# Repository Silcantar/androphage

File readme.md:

# Androphage

There have been keyboards that are portable and there have been keyboards that
have integrated pointing devices, but to date there haven't been any keyboards
that combine both features. With this new design I intend to change that.

I'm reaching the end of the design phase on my new keyboard, Androphage. It's a
folding unibody split keyboard with 44 keys and a finger trackball in the
center. When the keyboard is closed, all the more delicate components ---
switches, keycaps, screen --- are protected inside the rugged SLS nylon case.
Additionally the trackball is secured in-place by the folding base of the
keyboard.

## Highlights:

- Unibody with fixed 15° split angle\* and 10° tent angle.

- 44 keys: 3x5, plus 4 thumb keys, row 5\*\* middle and ring finger keys, and
  key that can either be a very tucked thumb key or a row 5 index finger key.

- Rugged SLS nylon case.

- NRF52850 microcontroller and ZMK firmware for Bluetooth, dongle, or wired
  connectivity.

- Dual-sensor 34mm trackball is capable of 3-axis control, i.e. twist-to-scroll
  à la Kensington SlimBlade.

- Nice!View or similar screen for layer, pairing, and charging status.

- Low power consumption microcontroller and trackball sensors (PMW3610) paired
  with a 300 mAh LiPo battery for days or weeks of battery life.

- USB-C charging and connectivity.

- Designed for Chicago Steno or KLP Lamé keycaps but can potentially be adapted
  for other low-to-mid-profile keycaps.

- The custom hinges are SLM stainless steel for maximum durability.

- There is space inside the base for storing the charging cable.

- Unfolded dimensions: 290 x 135 x 62 mm

- Folded dimensions: 148 x 135 x 45 mm

\* Measured between the centerline of the keyboard and the axis of the index
finger key column.

\*\* That is, two rows below the home row, equivalent to the modifier row on an
ANSI/ISO keyboard.

## Additional Renders

## Open Source

This project is licensed under the CERN Open Hardware License, Strongly
Reciprocal 2.0.

---

> *Well, I saw the thing comin' out of the sky*
>
> *It had a-one long horn and one big eye*
>
> *I commenced to shakin' and I said, "Ooh-eee!*
>
> *It looks like a purple people eater to me!"*
>
> &mdash;Sheb Wooley

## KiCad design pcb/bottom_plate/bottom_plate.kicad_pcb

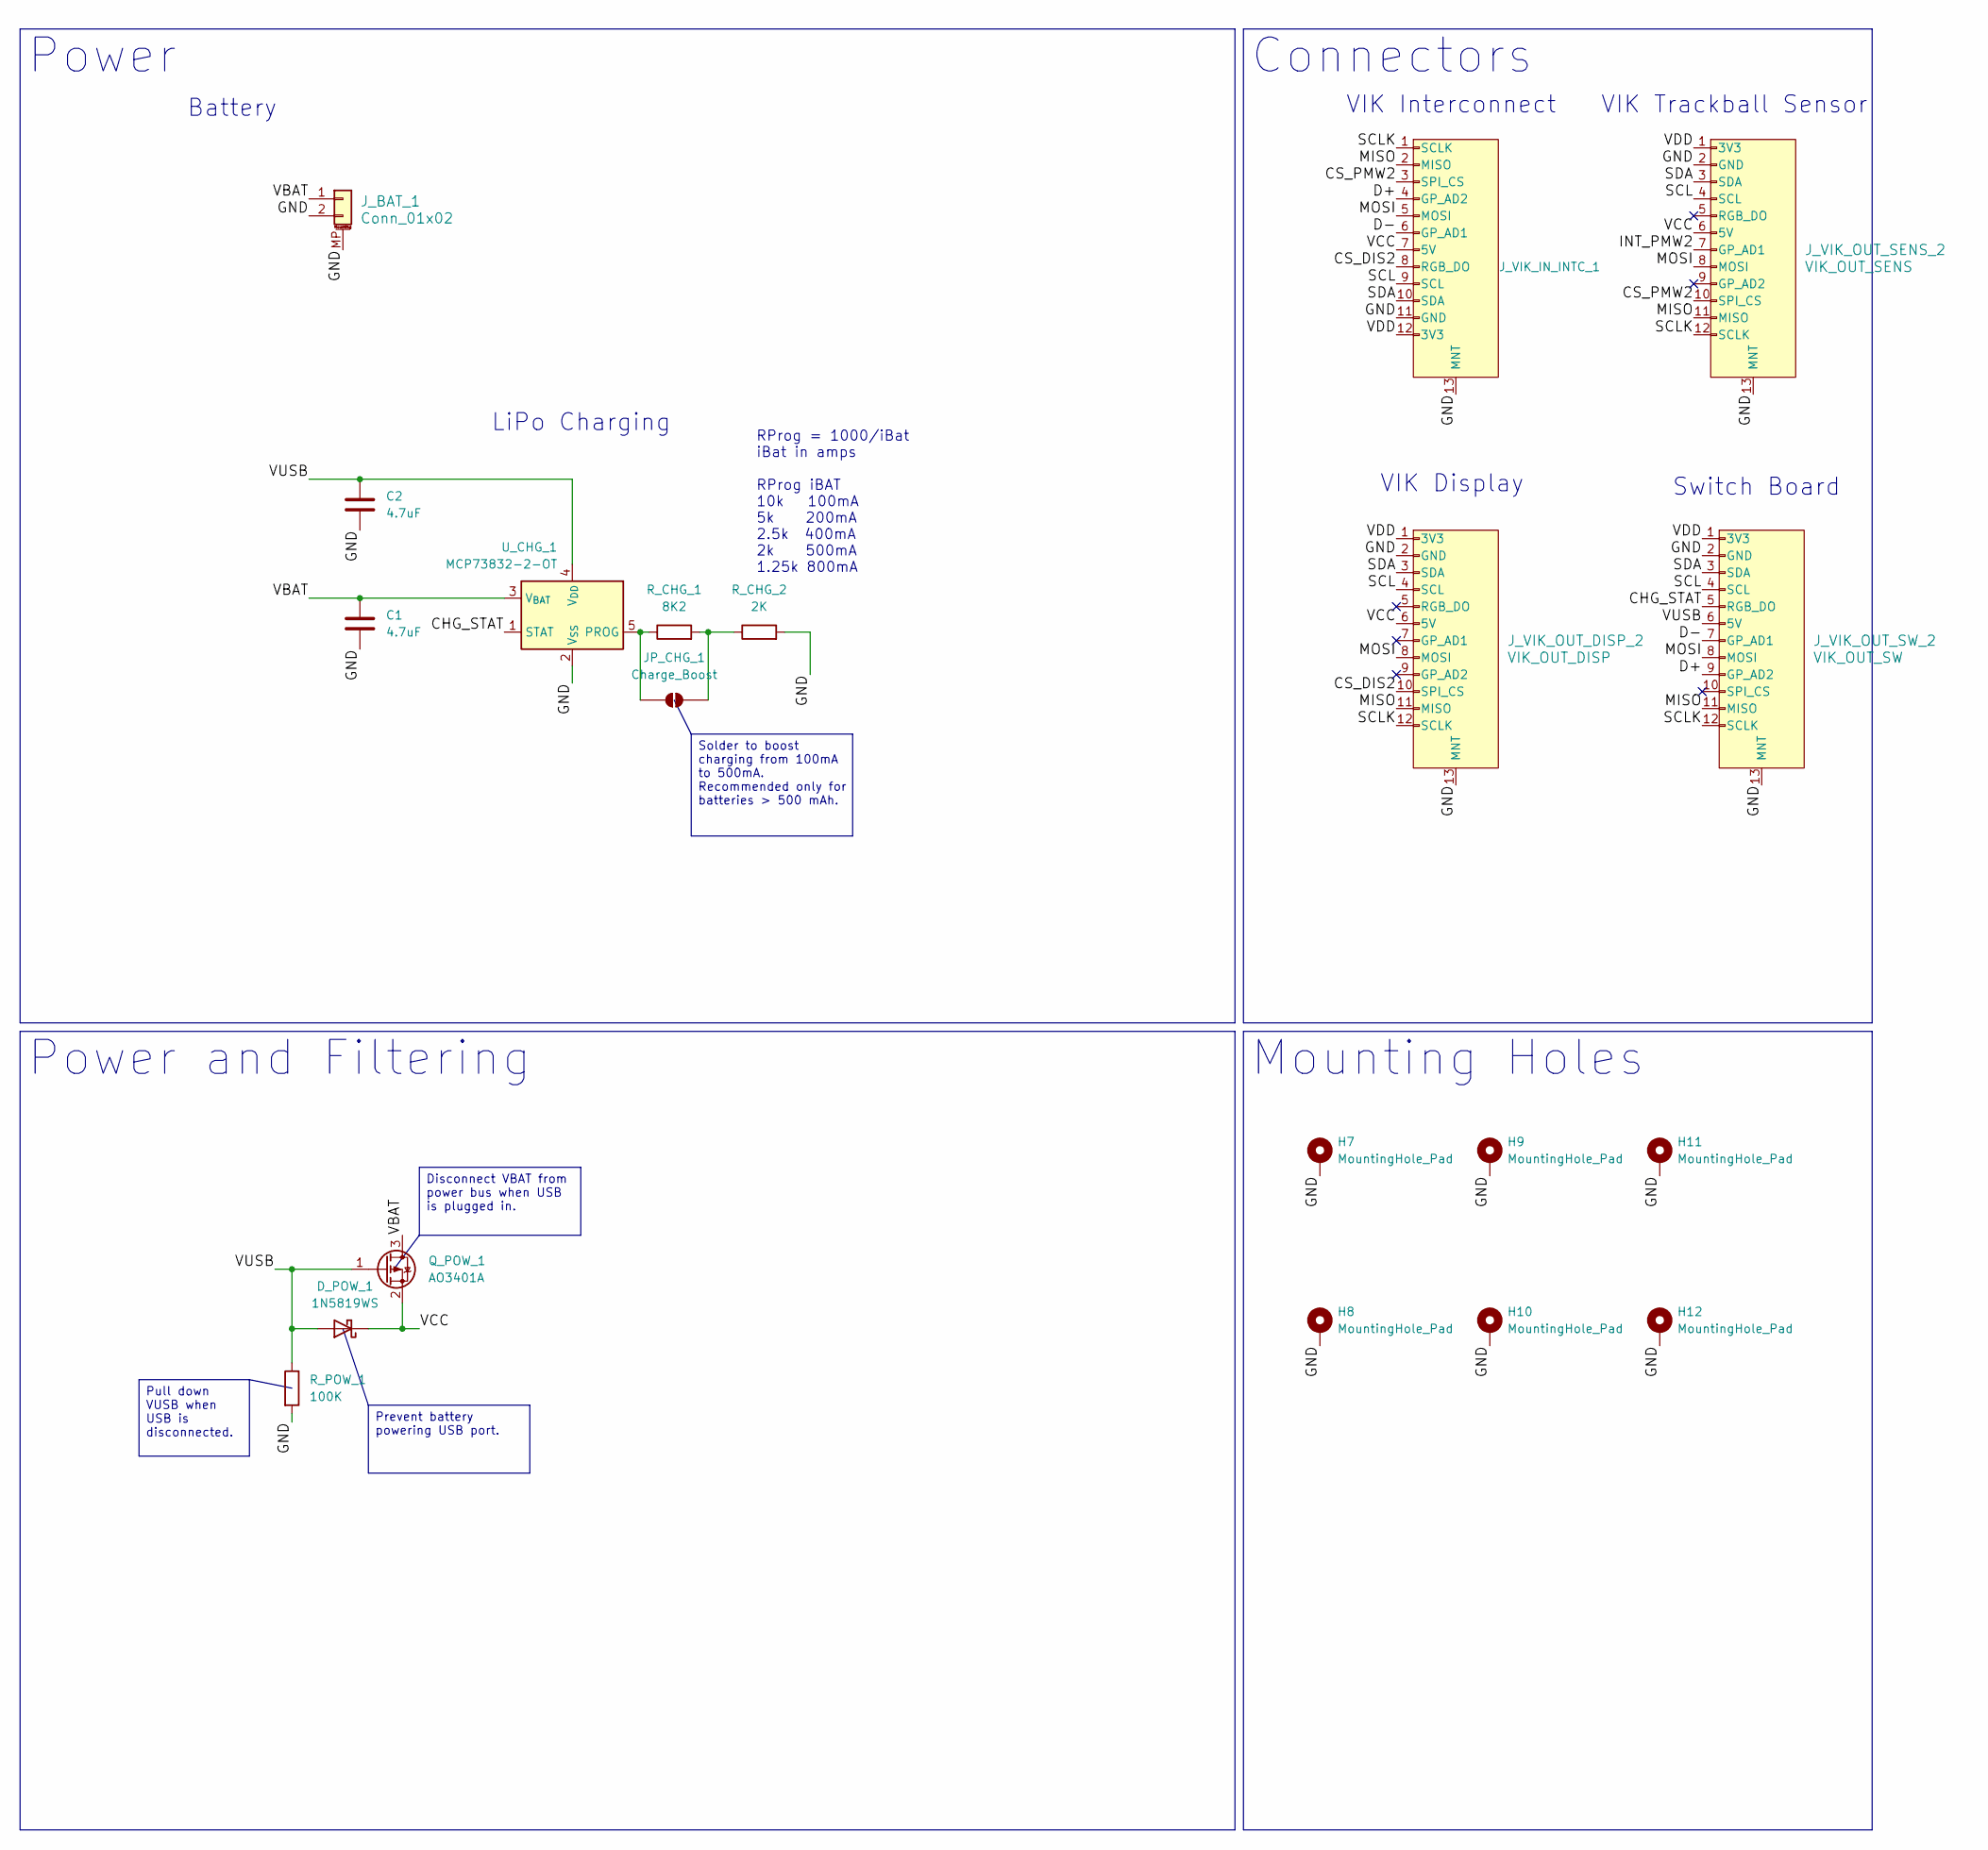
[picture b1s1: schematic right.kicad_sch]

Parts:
C1, C2: 4.7uF; C_0805_2012Metric_Pad1.18x1.45mm_HandSolder
D_POW_1: 1N5819WS; D_SOD-123
H7, H8, H9, H10, H11, H12: MountingHole_Pad; MountingHole_2.2mm_M2_Pad
JP_CHG_1: Charge_Boost; SolderJumper-2_P1.3mm_Open_RoundedPad1.0x1.5mm
J_BAT_1: Conn_01x02; JST_GH_SM02B-GHS-TB_1x02-1MP_P1.25mm_Horizontal
J_VIK_IN_INTC_1: vik-module-connector; vik-module-connector-horizontal
J_VIK_OUT_DISP_2: VIK_OUT_DISP; vik-keyboard-connector-horizontal
J_VIK_OUT_SENS_2: VIK_OUT_SENS; vik-keyboard-connector-horizontal
J_VIK_OUT_SW_2: VIK_OUT_SW; vik-keyboard-connector-horizontal
Q_POW_1: AO3401A; SOT-23
R_CHG_1: 8K2; R_0805_2012Metric_Pad1.20x1.40mm_HandSolder
R_CHG_2: 2K; R_0805_2012Metric_Pad1.20x1.40mm_HandSolder
R_POW_1: 100K; R_0805_2012Metric_Pad1.20x1.40mm_HandSolder
U_CHG_1: MCP73832-2-OT; SOT-23-5

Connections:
/Right/CHG_STAT: J_VIK_OUT_SW_2.5 (RGB_DO), U_CHG_1.1 (STAT)
/Right/CS_DIS2: J_VIK_IN_INTC_1.8 (RGB_DO), J_VIK_OUT_DISP_2.10 (SPI_CS)
/Right/CS_PMW2: J_VIK_IN_INTC_1.3 (SPI_CS), J_VIK_OUT_SENS_2.10 (SPI_CS)
/Right/D+: J_VIK_IN_INTC_1.4 (GP_AD2), J_VIK_OUT_SW_2.9 (GP_AD2)
/Right/D-: J_VIK_IN_INTC_1.6 (GP_AD1), J_VIK_OUT_SW_2.7 (GP_AD1)
/Right/GND: C1.2, C2.2, H7.1 (1_1), H8.1 (1_1), H9.1 (1_1), H10.1 (1_1), H11.1 (1_1), H12.1 (1_1), J_BAT_1.2, J_BAT_1.MP (MountPin), J_VIK_IN_INTC_1.11 (GND), J_VIK_IN_INTC_1.13 (MNT), J_VIK_OUT_DISP_2.2 (GND), J_VIK_OUT_DISP_2.13 (MNT), J_VIK_OUT_SENS_2.2 (GND), J_VIK_OUT_SENS_2.13 (MNT), J_VIK_OUT_SW_2.2 (GND), J_VIK_OUT_SW_2.13 (MNT), R_CHG_2.2, R_POW_1.2, U_CHG_1.2 (V_{SS})
/Right/INT_PMW2: J_VIK_OUT_SENS_2.7 (GP_AD1)
/Right/MISO: J_VIK_IN_INTC_1.2 (MISO), J_VIK_OUT_DISP_2.11 (MISO), J_VIK_OUT_SENS_2.11 (MISO), J_VIK_OUT_SW_2.11 (MISO)
/Right/MOSI: J_VIK_IN_INTC_1.5 (MOSI), J_VIK_OUT_DISP_2.8 (MOSI), J_VIK_OUT_SENS_2.8 (MOSI), J_VIK_OUT_SW_2.8 (MOSI)
/Right/SCL: J_VIK_IN_INTC_1.9 (SCL), J_VIK_OUT_DISP_2.4 (SCL), J_VIK_OUT_SENS_2.4 (SCL), J_VIK_OUT_SW_2.4 (SCL)
/Right/SCLK: J_VIK_IN_INTC_1.1 (SCLK), J_VIK_OUT_DISP_2.12 (SCLK), J_VIK_OUT_SENS_2.12 (SCLK), J_VIK_OUT_SW_2.12 (SCLK)
/Right/SDA: J_VIK_IN_INTC_1.10 (SDA), J_VIK_OUT_DISP_2.3 (SDA), J_VIK_OUT_SENS_2.3 (SDA), J_VIK_OUT_SW_2.3 (SDA)
/Right/VBAT: C1.1, J_BAT_1.1, Q_POW_1.3 (D), U_CHG_1.3 (V_{BAT})
/Right/VCC: D_POW_1.1 (K), J_VIK_IN_INTC_1.7 (5V), J_VIK_OUT_DISP_2.6 (5V), J_VIK_OUT_SENS_2.6 (5V), Q_POW_1.2 (S)
/Right/VDD: J_VIK_IN_INTC_1.12 (3V3), J_VIK_OUT_DISP_2.1 (3V3), J_VIK_OUT_SENS_2.1 (3V3), J_VIK_OUT_SW_2.1 (3V3)
/Right/VUSB: C2.1, D_POW_1.2 (A), J_VIK_OUT_SW_2.6 (5V), Q_POW_1.1 (G), R_POW_1.1, U_CHG_1.4 (V_{DD})
unnamed: JP_CHG_1.1 (A), R_CHG_1.1, U_CHG_1.5 (PROG)
unnamed: JP_CHG_1.2 (B), R_CHG_1.2, R_CHG_2.1

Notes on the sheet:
LiPo Charging
VIK Trackball Sensor
RProg = 1000/iBat iBat in amps RProg iBAT 10k 100mA 5k 200mA 2.5k 400mA 2k 500mA 1.25k 800mA
Switch Board
Battery
VIK Interconnect
VIK Display
Power
Solder to boost charging from 100mA to 500mA. Recommended only for batteries > 500 mAh.
Mounting Holes
Pull down VUSB when USB is disconnected.
Disconnect VBAT from power bus when USB is plugged in.
Prevent battery powering USB port.
Power and Filtering
Connectors

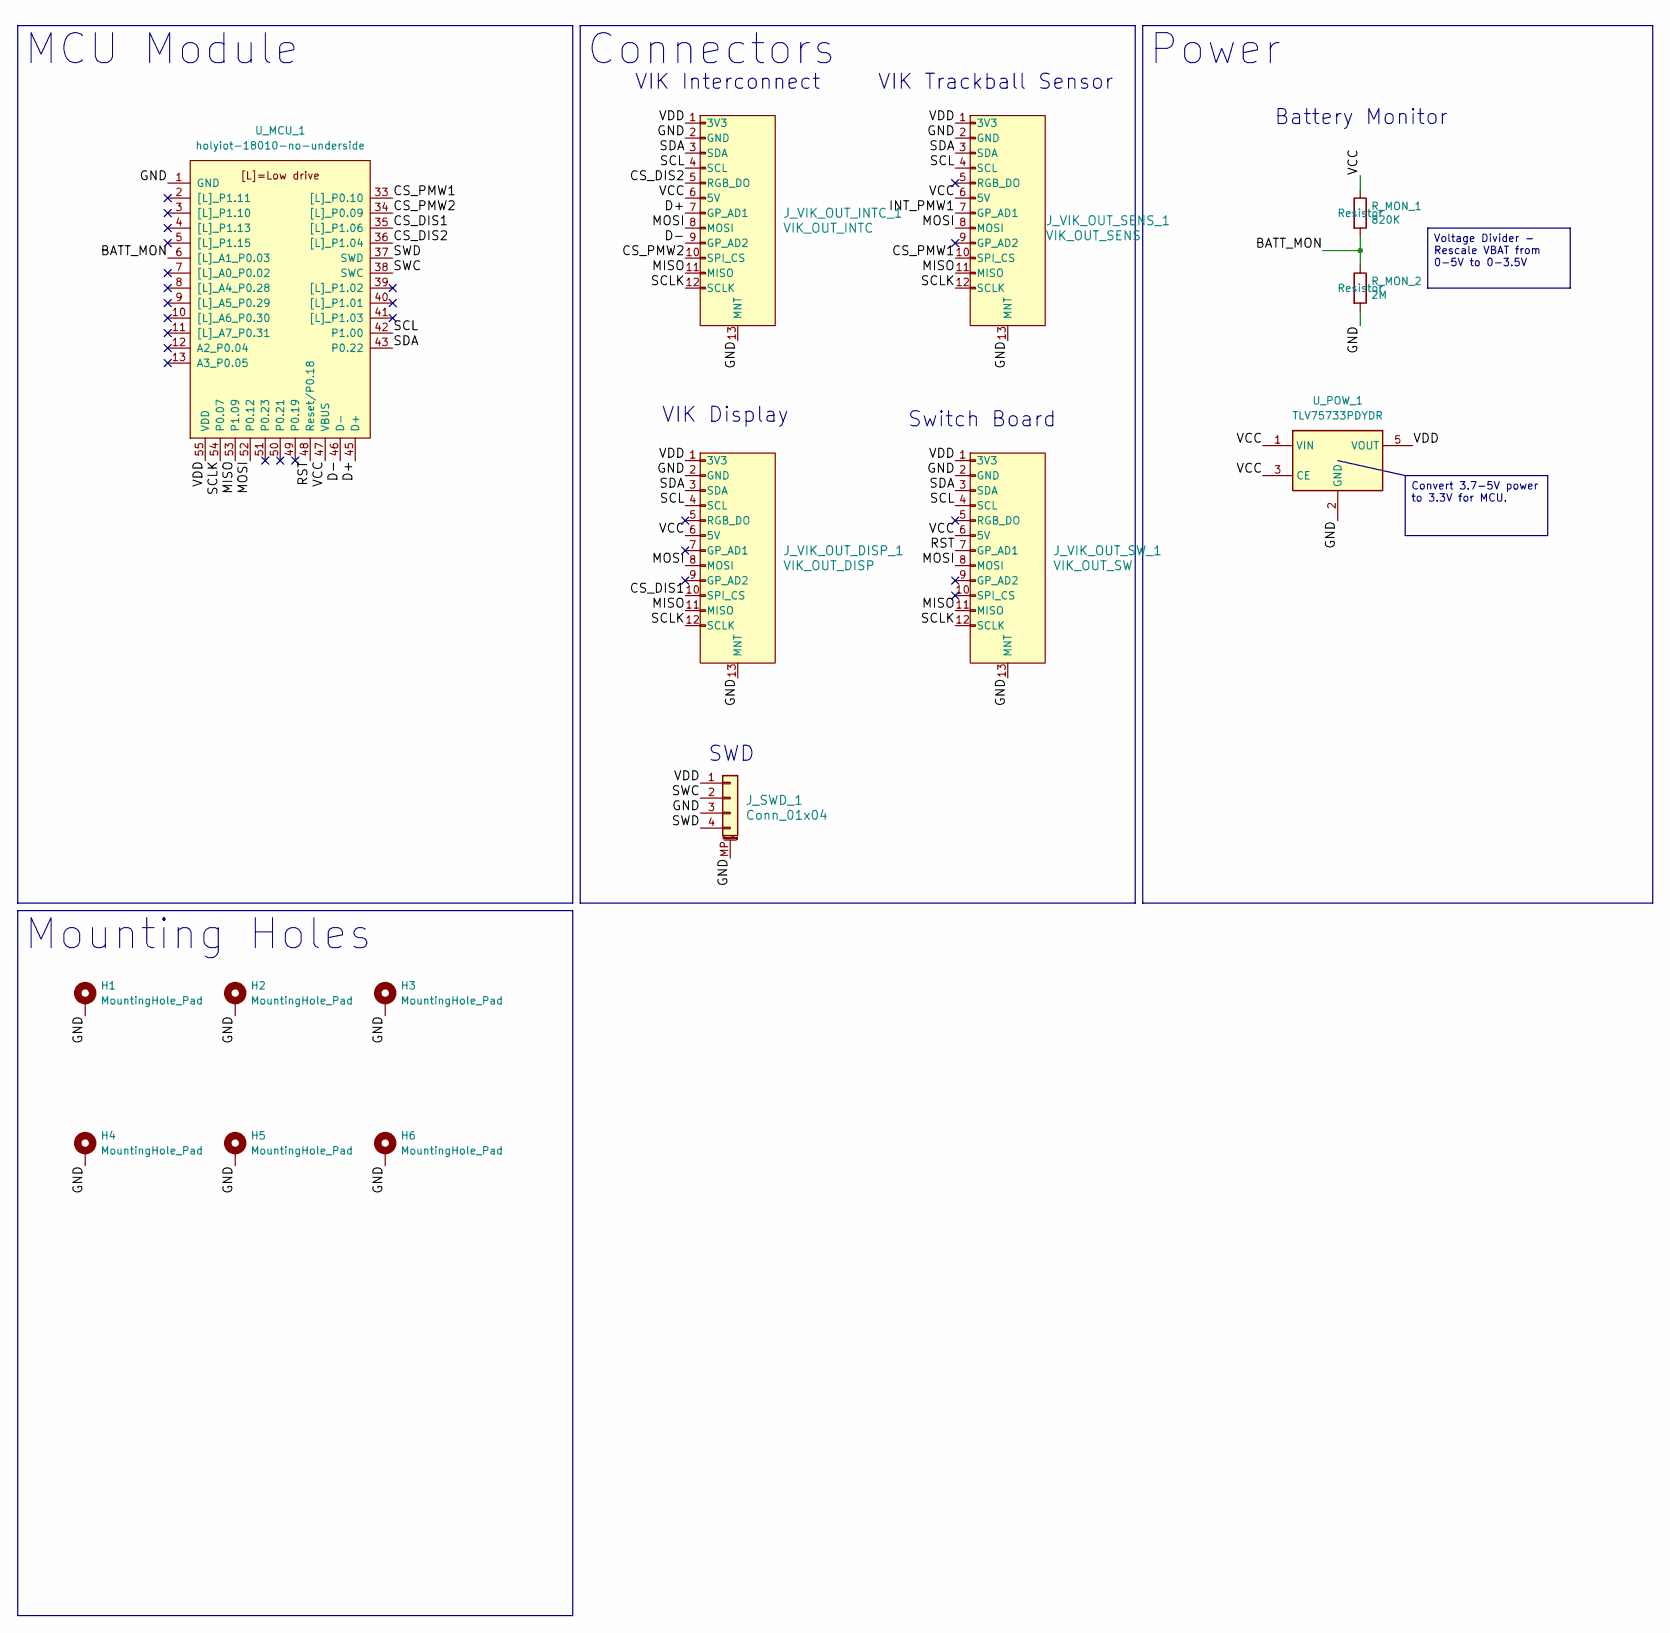
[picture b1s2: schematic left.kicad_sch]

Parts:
H1, H2, H3, H4, H5, H6: MountingHole_Pad; MountingHole_2.2mm_M2_Pad
J_SWD_1: Conn_01x04; JST_GH_SM04B-GHS-TB_1x04-1MP_P1.25mm_Horizontal
J_VIK_OUT_DISP_1: VIK_OUT_DISP; vik-keyboard-connector-horizontal
J_VIK_OUT_INTC_1: VIK_OUT_INTC; vik-keyboard-connector-horizontal
J_VIK_OUT_SENS_1: VIK_OUT_SENS; vik-keyboard-connector-horizontal
J_VIK_OUT_SW_1: VIK_OUT_SW; vik-keyboard-connector-horizontal
R_MON_1: 820K; R_0805_2012Metric_Pad1.20x1.40mm_HandSolder
R_MON_2: 2M; R_0805_2012Metric_Pad1.20x1.40mm_HandSolder
U_MCU_1: holyiot-18010-no-underside
U_POW_1: TLV75733PDYDR; SOT-23-5; LCSC C22399950

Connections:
/Left/BATT_MON: R_MON_1.2, R_MON_2.1, U_MCU_1.6 ([L]_A1_P0.03)
/Left/CS_DIS1: J_VIK_OUT_DISP_1.10 (SPI_CS), U_MCU_1.35 ([L]_P1.06)
/Left/CS_DIS2: J_VIK_OUT_INTC_1.5 (RGB_DO), U_MCU_1.36 ([L]_P1.04)
/Left/CS_PMW1: J_VIK_OUT_SENS_1.10 (SPI_CS), U_MCU_1.33 ([L]_P0.10)
/Left/CS_PMW2: J_VIK_OUT_INTC_1.10 (SPI_CS), U_MCU_1.34 ([L]_P0.09)
/Left/D+: J_VIK_OUT_INTC_1.7 (GP_AD1), U_MCU_1.45 (D+)
/Left/D-: J_VIK_OUT_INTC_1.9 (GP_AD2), U_MCU_1.46 (D-)
/Left/GND: H1.1 (1_1), H2.1 (1_1), H3.1 (1_1), H4.1 (1_1), H5.1 (1_1), H6.1 (1_1), J_SWD_1.3, J_SWD_1.MP (MountPin), J_VIK_OUT_DISP_1.2 (GND), J_VIK_OUT_DISP_1.13 (MNT), J_VIK_OUT_INTC_1.2 (GND), J_VIK_OUT_INTC_1.13 (MNT), J_VIK_OUT_SENS_1.2 (GND), J_VIK_OUT_SENS_1.13 (MNT), J_VIK_OUT_SW_1.2 (GND), J_VIK_OUT_SW_1.13 (MNT), R_MON_2.2, U_MCU_1.1 (GND), U_MCU_1.32 (GND), U_MCU_1.44 (GND), U_POW_1.2 (GND)
/Left/INT_PMW1: J_VIK_OUT_SENS_1.7 (GP_AD1)
/Left/MISO: J_VIK_OUT_DISP_1.11 (MISO), J_VIK_OUT_INTC_1.11 (MISO), J_VIK_OUT_SENS_1.11 (MISO), J_VIK_OUT_SW_1.11 (MISO), U_MCU_1.53 (P1.09)
/Left/MOSI: J_VIK_OUT_DISP_1.8 (MOSI), J_VIK_OUT_INTC_1.8 (MOSI), J_VIK_OUT_SENS_1.8 (MOSI), J_VIK_OUT_SW_1.8 (MOSI), U_MCU_1.52 (P0.12)
/Left/RST: J_VIK_OUT_SW_1.7 (GP_AD1), U_MCU_1.48 (Reset/P0.18)
/Left/SCL: J_VIK_OUT_DISP_1.4 (SCL), J_VIK_OUT_INTC_1.4 (SCL), J_VIK_OUT_SENS_1.4 (SCL), J_VIK_OUT_SW_1.4 (SCL), U_MCU_1.42 (P1.00)
/Left/SCLK: J_VIK_OUT_DISP_1.12 (SCLK), J_VIK_OUT_INTC_1.12 (SCLK), J_VIK_OUT_SENS_1.12 (SCLK), J_VIK_OUT_SW_1.12 (SCLK), U_MCU_1.54 (P0.07)
/Left/SDA: J_VIK_OUT_DISP_1.3 (SDA), J_VIK_OUT_INTC_1.3 (SDA), J_VIK_OUT_SENS_1.3 (SDA), J_VIK_OUT_SW_1.3 (SDA), U_MCU_1.43 (P0.22)
/Left/SWC: J_SWD_1.2, U_MCU_1.38 (SWC)
/Left/SWD: J_SWD_1.4, U_MCU_1.37 (SWD)
/Left/VCC: J_VIK_OUT_DISP_1.6 (5V), J_VIK_OUT_INTC_1.6 (5V), J_VIK_OUT_SENS_1.6 (5V), J_VIK_OUT_SW_1.6 (5V), R_MON_1.1, U_MCU_1.47 (VBUS), U_POW_1.1 (VIN), U_POW_1.3 (CE)
/Left/VDD: J_SWD_1.1, J_VIK_OUT_DISP_1.1 (3V3), J_VIK_OUT_INTC_1.1 (3V3), J_VIK_OUT_SENS_1.1 (3V3), J_VIK_OUT_SW_1.1 (3V3), U_MCU_1.55 (VDD), U_POW_1.5 (VOUT)

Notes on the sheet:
Switch Board
VIK Trackball Sensor
Battery Monitor
SWD
VIK Display
VIK Interconnect
Voltage Divider - Rescale VBAT from 0-5V to 0-3.5V
Convert 3.7-5V power to 3.3V for MCU.
MCU Module
Connectors
Mounting Holes
Power

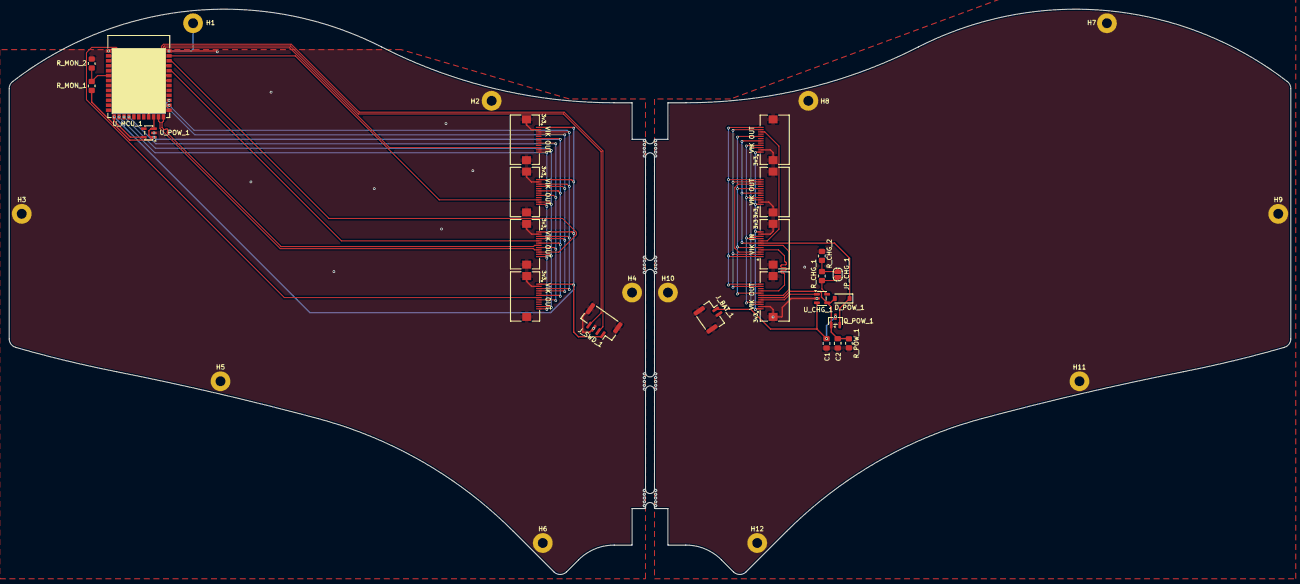
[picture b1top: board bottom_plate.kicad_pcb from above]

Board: 2 copper layers, 285.8 x 126.1 mm, 35 parts (0 on the bottom side), 35 nets.

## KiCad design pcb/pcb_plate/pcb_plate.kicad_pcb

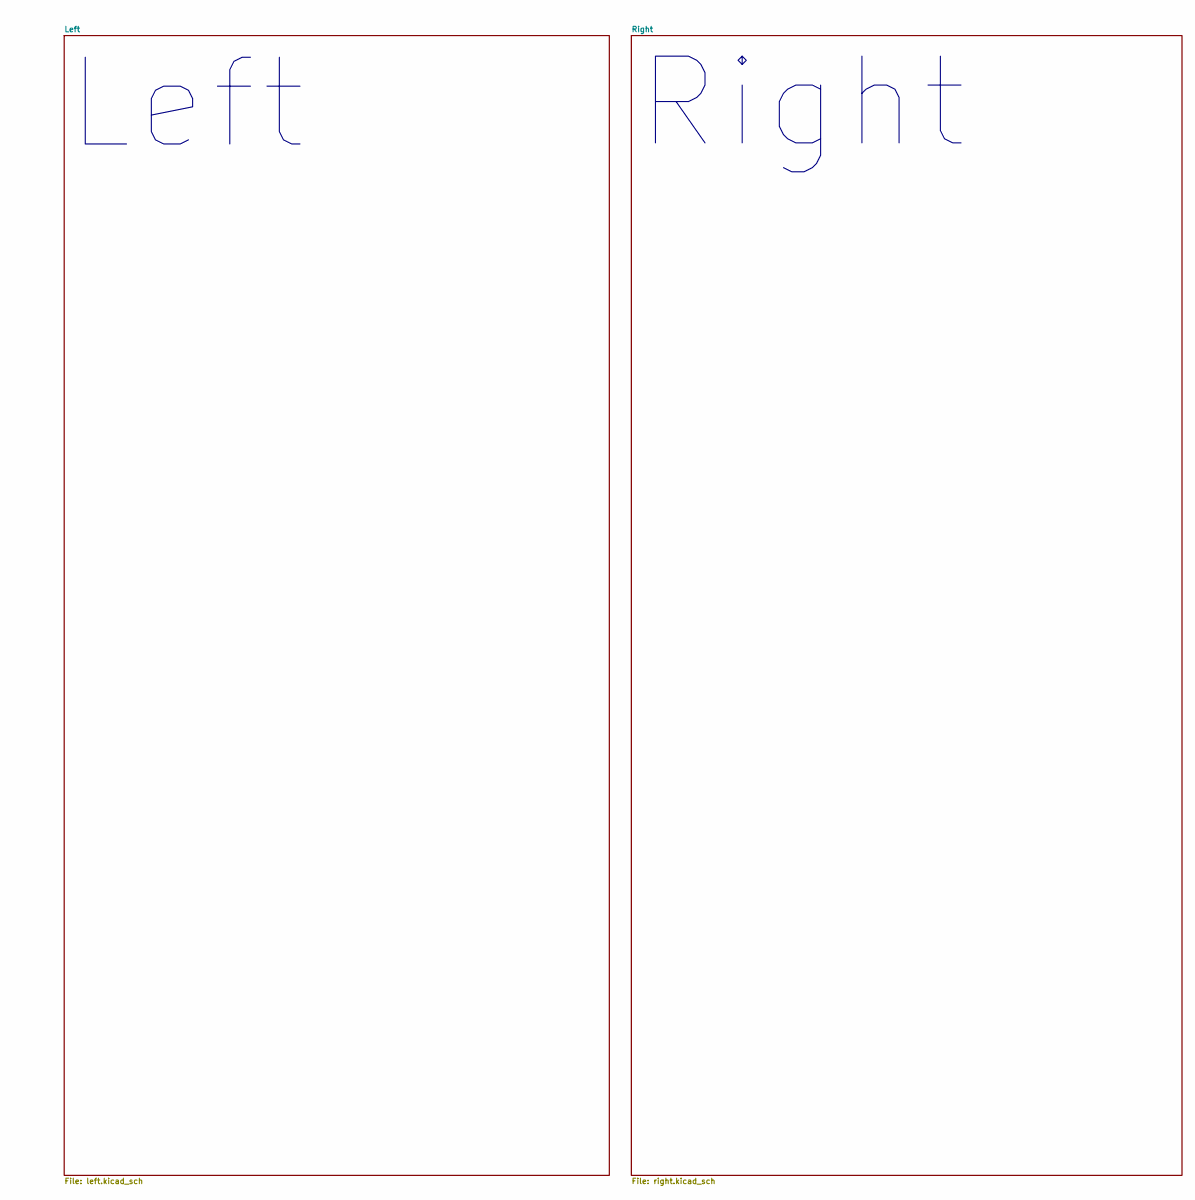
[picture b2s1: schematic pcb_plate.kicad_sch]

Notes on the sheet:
Right
Left

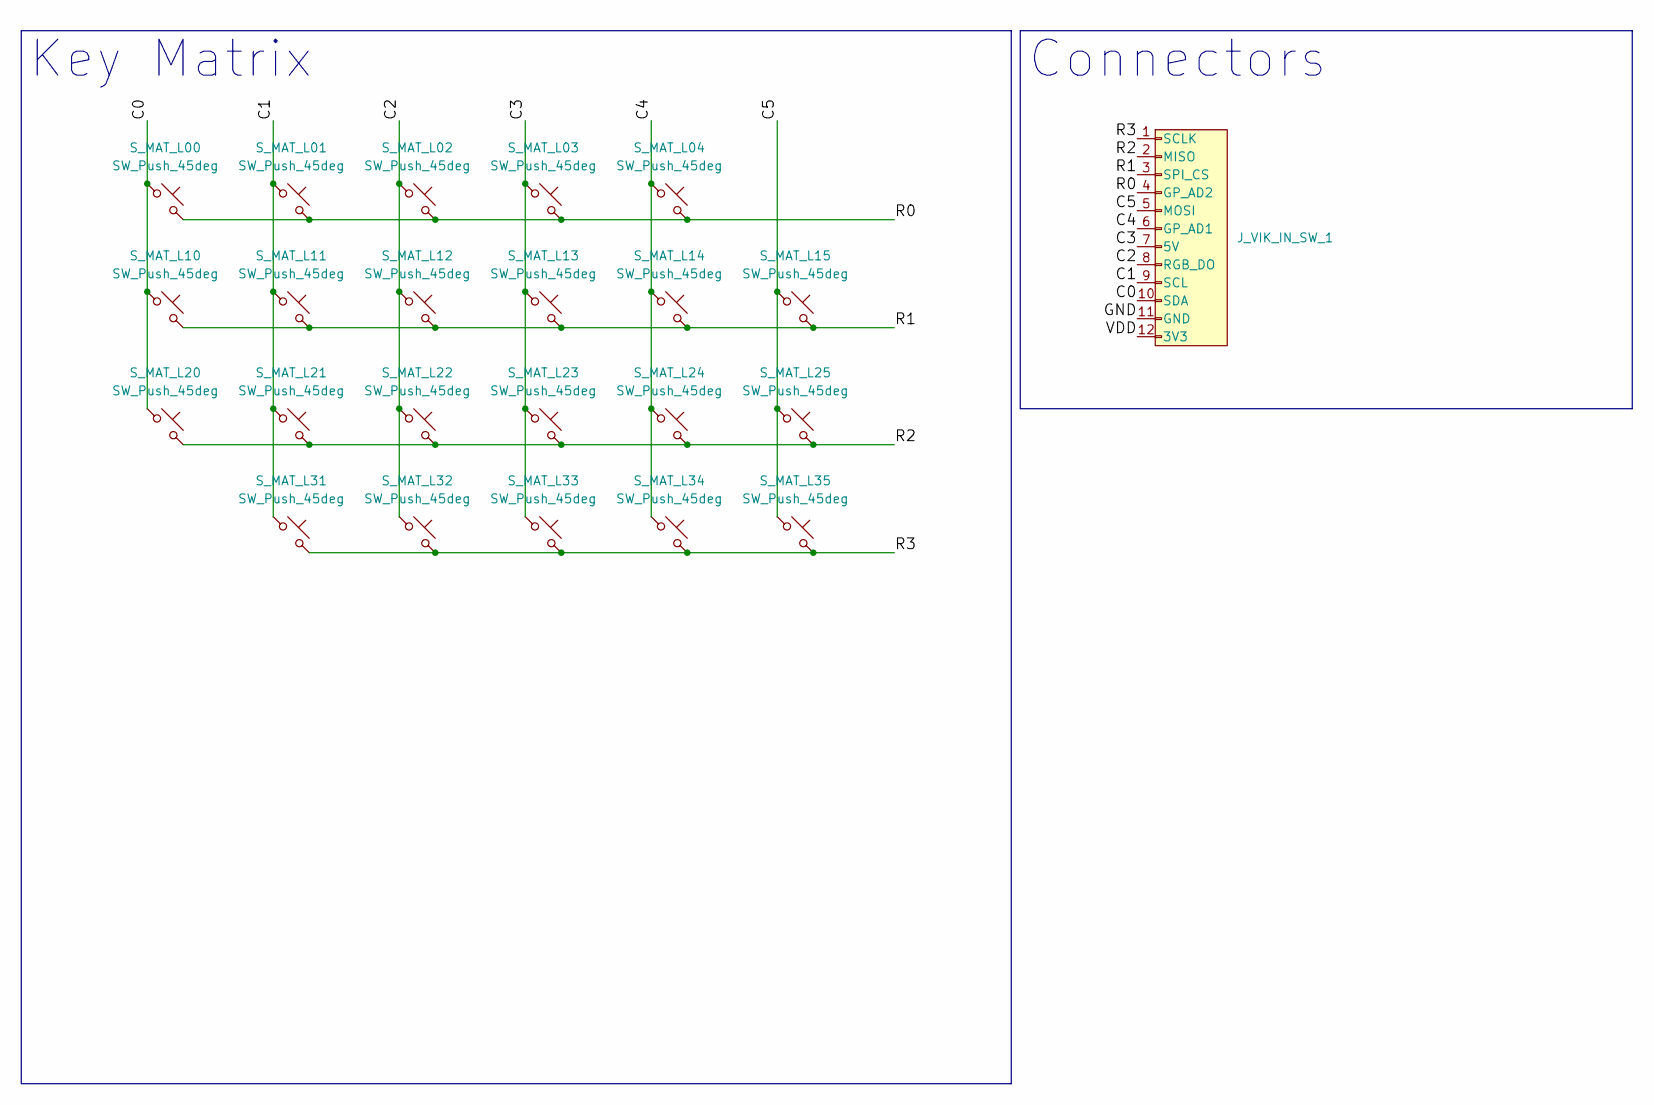
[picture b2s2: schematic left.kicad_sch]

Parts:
J_VIK_IN_SW_1: vik-module-connector; vik-module-connector-horizontal
S_MAT_L00, S_MAT_L01, S_MAT_L02, S_MAT_L03, S_MAT_L04, S_MAT_L10, S_MAT_L11, S_MAT_L12, S_MAT_L13, S_MAT_L14, S_MAT_L15, S_MAT_L20, S_MAT_L21, S_MAT_L22, S_MAT_L23, S_MAT_L24, S_MAT_L25, S_MAT_L31, S_MAT_L32, S_MAT_L33, S_MAT_L34, S_MAT_L35: SW_Push_45deg; SW_GLP_Kailh_Choc_V1V2_HotSwap_PTH

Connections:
/Left/C0: J_VIK_IN_SW_1.10 (SDA), S_MAT_L00.1, S_MAT_L10.1, S_MAT_L20.1
/Left/C1: J_VIK_IN_SW_1.9 (SCL), S_MAT_L01.1, S_MAT_L11.1, S_MAT_L21.1, S_MAT_L31.1
/Left/C2: J_VIK_IN_SW_1.8 (RGB_DO), S_MAT_L02.1, S_MAT_L12.1, S_MAT_L22.1, S_MAT_L32.1
/Left/C3: J_VIK_IN_SW_1.7 (5V), S_MAT_L03.1, S_MAT_L13.1, S_MAT_L23.1, S_MAT_L33.1
/Left/C4: J_VIK_IN_SW_1.6 (GP_AD1), S_MAT_L04.1, S_MAT_L14.1, S_MAT_L24.1, S_MAT_L34.1
/Left/C5: J_VIK_IN_SW_1.5 (MOSI), S_MAT_L15.1, S_MAT_L25.1, S_MAT_L35.1
/Left/GND: J_VIK_IN_SW_1.11 (GND), J_VIK_IN_SW_1.13, J_VIK_IN_SW_1.14
/Left/R0: J_VIK_IN_SW_1.4 (GP_AD2), S_MAT_L00.2, S_MAT_L01.2, S_MAT_L02.2, S_MAT_L03.2, S_MAT_L04.2
/Left/R1: J_VIK_IN_SW_1.3 (SPI_CS), S_MAT_L10.2, S_MAT_L11.2, S_MAT_L12.2, S_MAT_L13.2, S_MAT_L14.2, S_MAT_L15.2
/Left/R2: J_VIK_IN_SW_1.2 (MISO), S_MAT_L20.2, S_MAT_L21.2, S_MAT_L22.2, S_MAT_L23.2, S_MAT_L24.2, S_MAT_L25.2
/Left/R3: J_VIK_IN_SW_1.1 (SCLK), S_MAT_L31.2, S_MAT_L32.2, S_MAT_L33.2, S_MAT_L34.2, S_MAT_L35.2
/Left/VDD: J_VIK_IN_SW_1.12 (3V3)

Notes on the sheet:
Connectors
Key Matrix

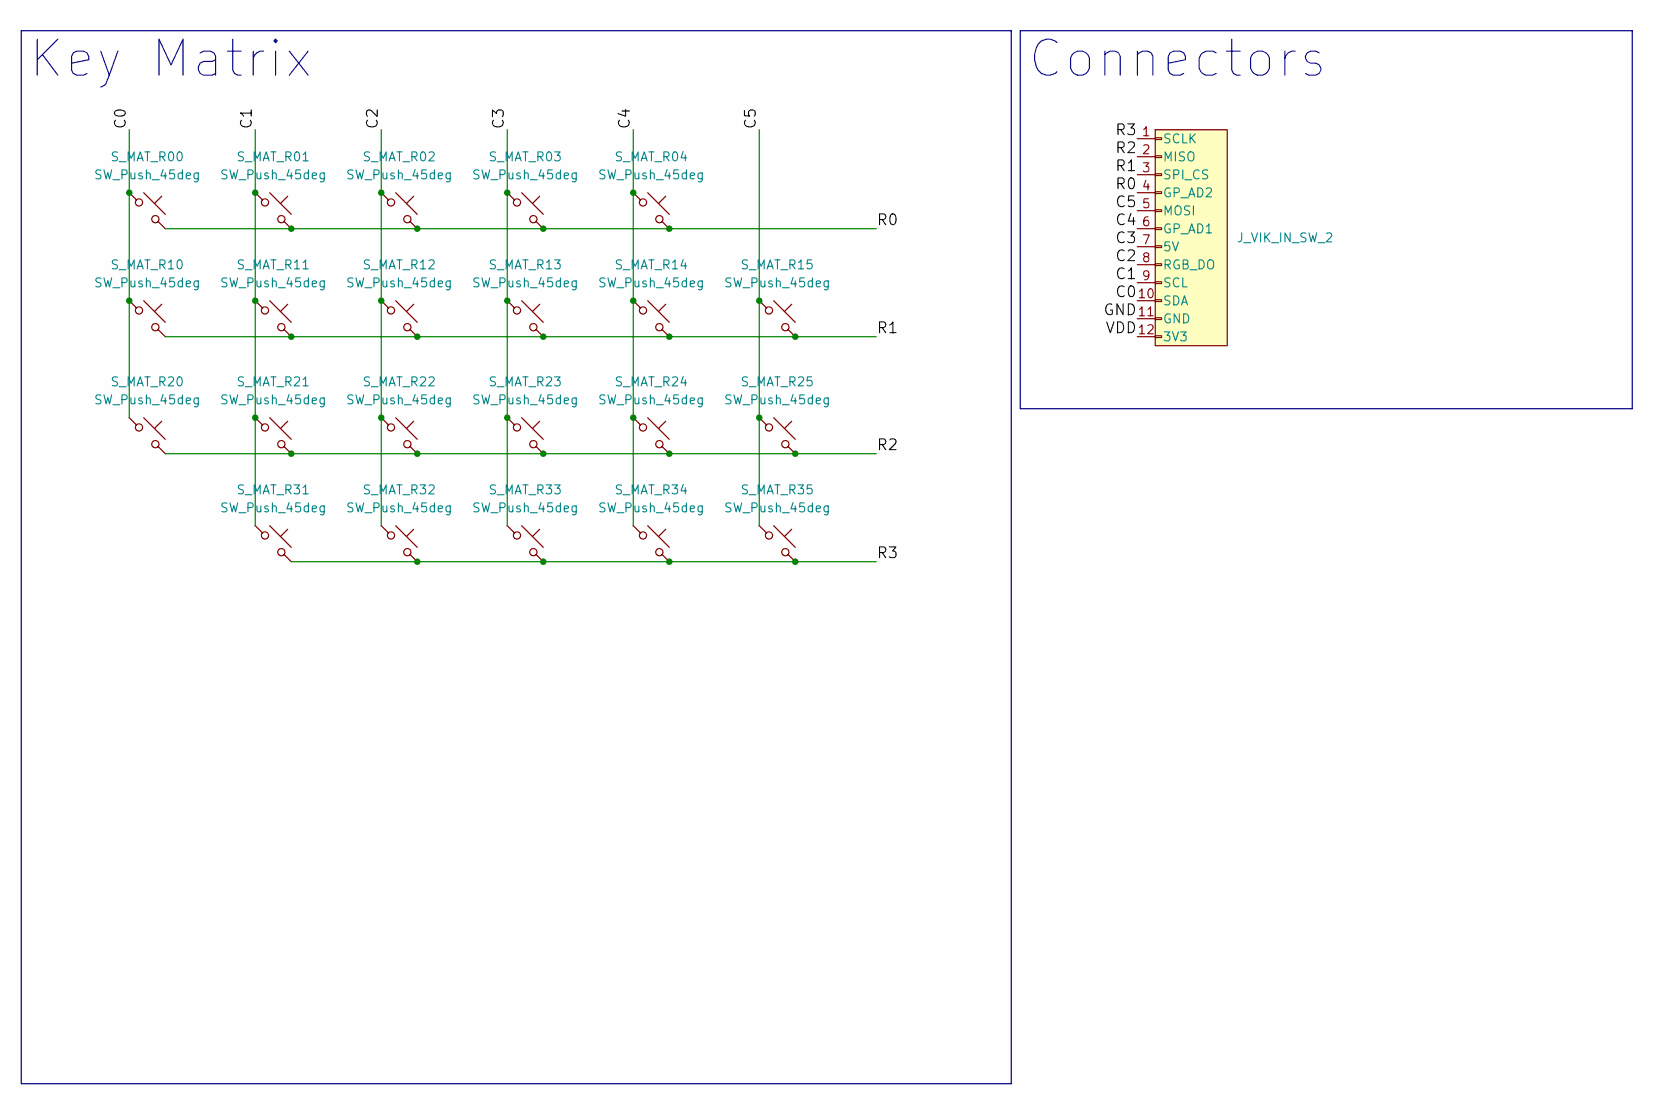
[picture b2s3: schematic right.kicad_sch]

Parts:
J_VIK_IN_SW_2: vik-module-connector; vik-module-connector-horizontal
S_MAT_R00, S_MAT_R01, S_MAT_R02, S_MAT_R03, S_MAT_R04, S_MAT_R10, S_MAT_R11, S_MAT_R12, S_MAT_R13, S_MAT_R14, S_MAT_R15, S_MAT_R20, S_MAT_R21, S_MAT_R22, S_MAT_R23, S_MAT_R24, S_MAT_R25, S_MAT_R31, S_MAT_R32, S_MAT_R33, S_MAT_R34, S_MAT_R35: SW_Push_45deg; SW_GLP_Kailh_Choc_V1V2_HotSwap_PTH

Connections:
/Right/C0: J_VIK_IN_SW_2.10 (SDA), S_MAT_R00.1, S_MAT_R10.1, S_MAT_R20.1
/Right/C1: J_VIK_IN_SW_2.9 (SCL), S_MAT_R01.1, S_MAT_R11.1, S_MAT_R21.1, S_MAT_R31.1
/Right/C2: J_VIK_IN_SW_2.8 (RGB_DO), S_MAT_R02.1, S_MAT_R12.1, S_MAT_R22.1, S_MAT_R32.1
/Right/C3: J_VIK_IN_SW_2.7 (5V), S_MAT_R03.1, S_MAT_R13.1, S_MAT_R23.1, S_MAT_R33.1
/Right/C4: J_VIK_IN_SW_2.6 (GP_AD1), S_MAT_R04.1, S_MAT_R14.1, S_MAT_R24.1, S_MAT_R34.1
/Right/C5: J_VIK_IN_SW_2.5 (MOSI), S_MAT_R15.1, S_MAT_R25.1, S_MAT_R35.1
/Right/GND: J_VIK_IN_SW_2.11 (GND), J_VIK_IN_SW_2.13, J_VIK_IN_SW_2.14
/Right/R0: J_VIK_IN_SW_2.4 (GP_AD2), S_MAT_R00.2, S_MAT_R01.2, S_MAT_R02.2, S_MAT_R03.2, S_MAT_R04.2
/Right/R1: J_VIK_IN_SW_2.3 (SPI_CS), S_MAT_R10.2, S_MAT_R11.2, S_MAT_R12.2, S_MAT_R13.2, S_MAT_R14.2, S_MAT_R15.2
/Right/R2: J_VIK_IN_SW_2.2 (MISO), S_MAT_R20.2, S_MAT_R21.2, S_MAT_R22.2, S_MAT_R23.2, S_MAT_R24.2, S_MAT_R25.2
/Right/R3: J_VIK_IN_SW_2.1 (SCLK), S_MAT_R31.2, S_MAT_R32.2, S_MAT_R33.2, S_MAT_R34.2, S_MAT_R35.2
/Right/VDD: J_VIK_IN_SW_2.12 (3V3)

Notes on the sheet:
Connectors
Key Matrix

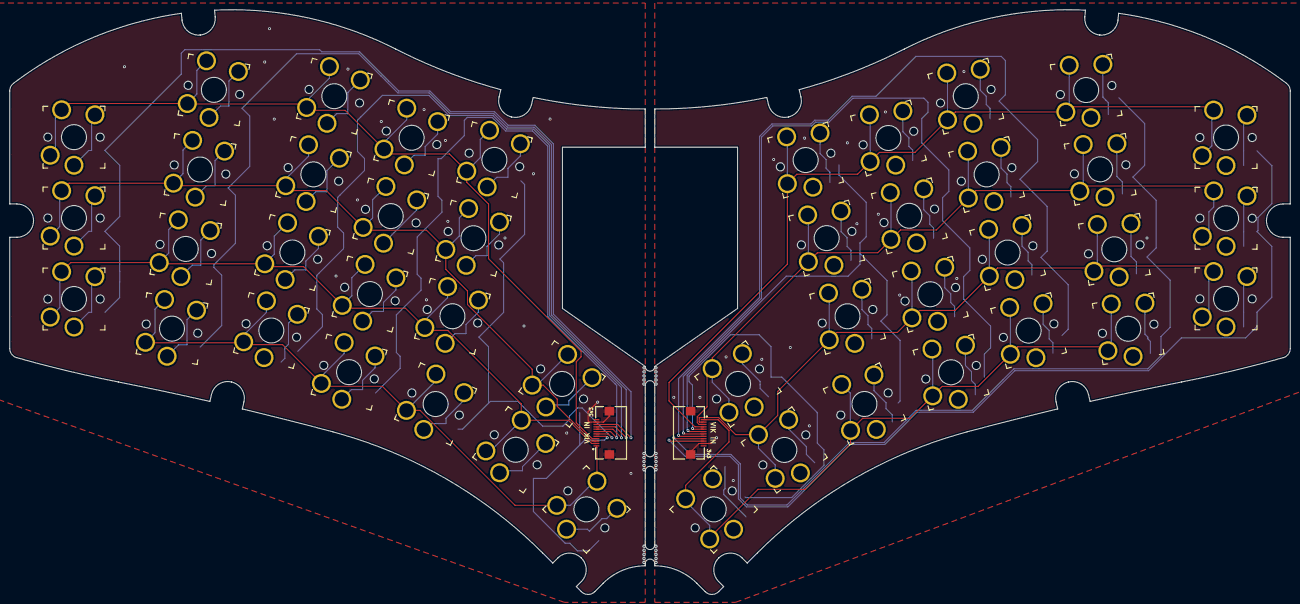
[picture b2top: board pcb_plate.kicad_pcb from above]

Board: 2 copper layers, 269.2 x 122.9 mm, 46 parts (0 on the bottom side), 22 nets.

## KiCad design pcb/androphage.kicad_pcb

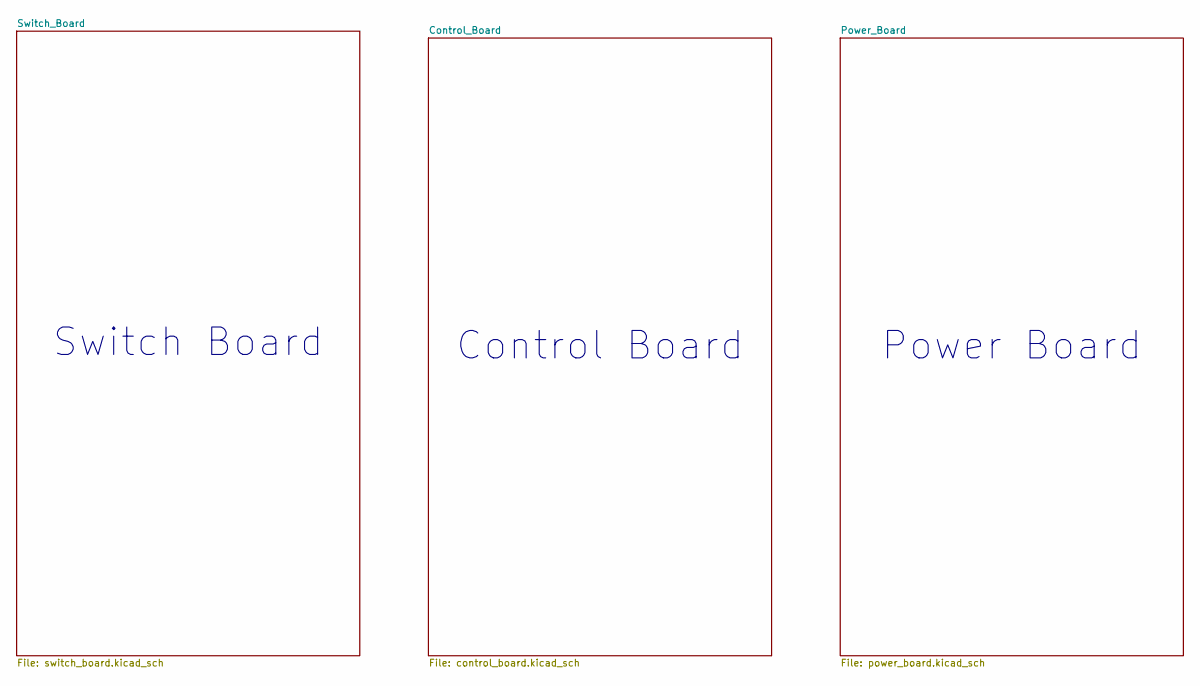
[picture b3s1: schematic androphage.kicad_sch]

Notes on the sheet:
Control Board
Switch Board
Power Board
